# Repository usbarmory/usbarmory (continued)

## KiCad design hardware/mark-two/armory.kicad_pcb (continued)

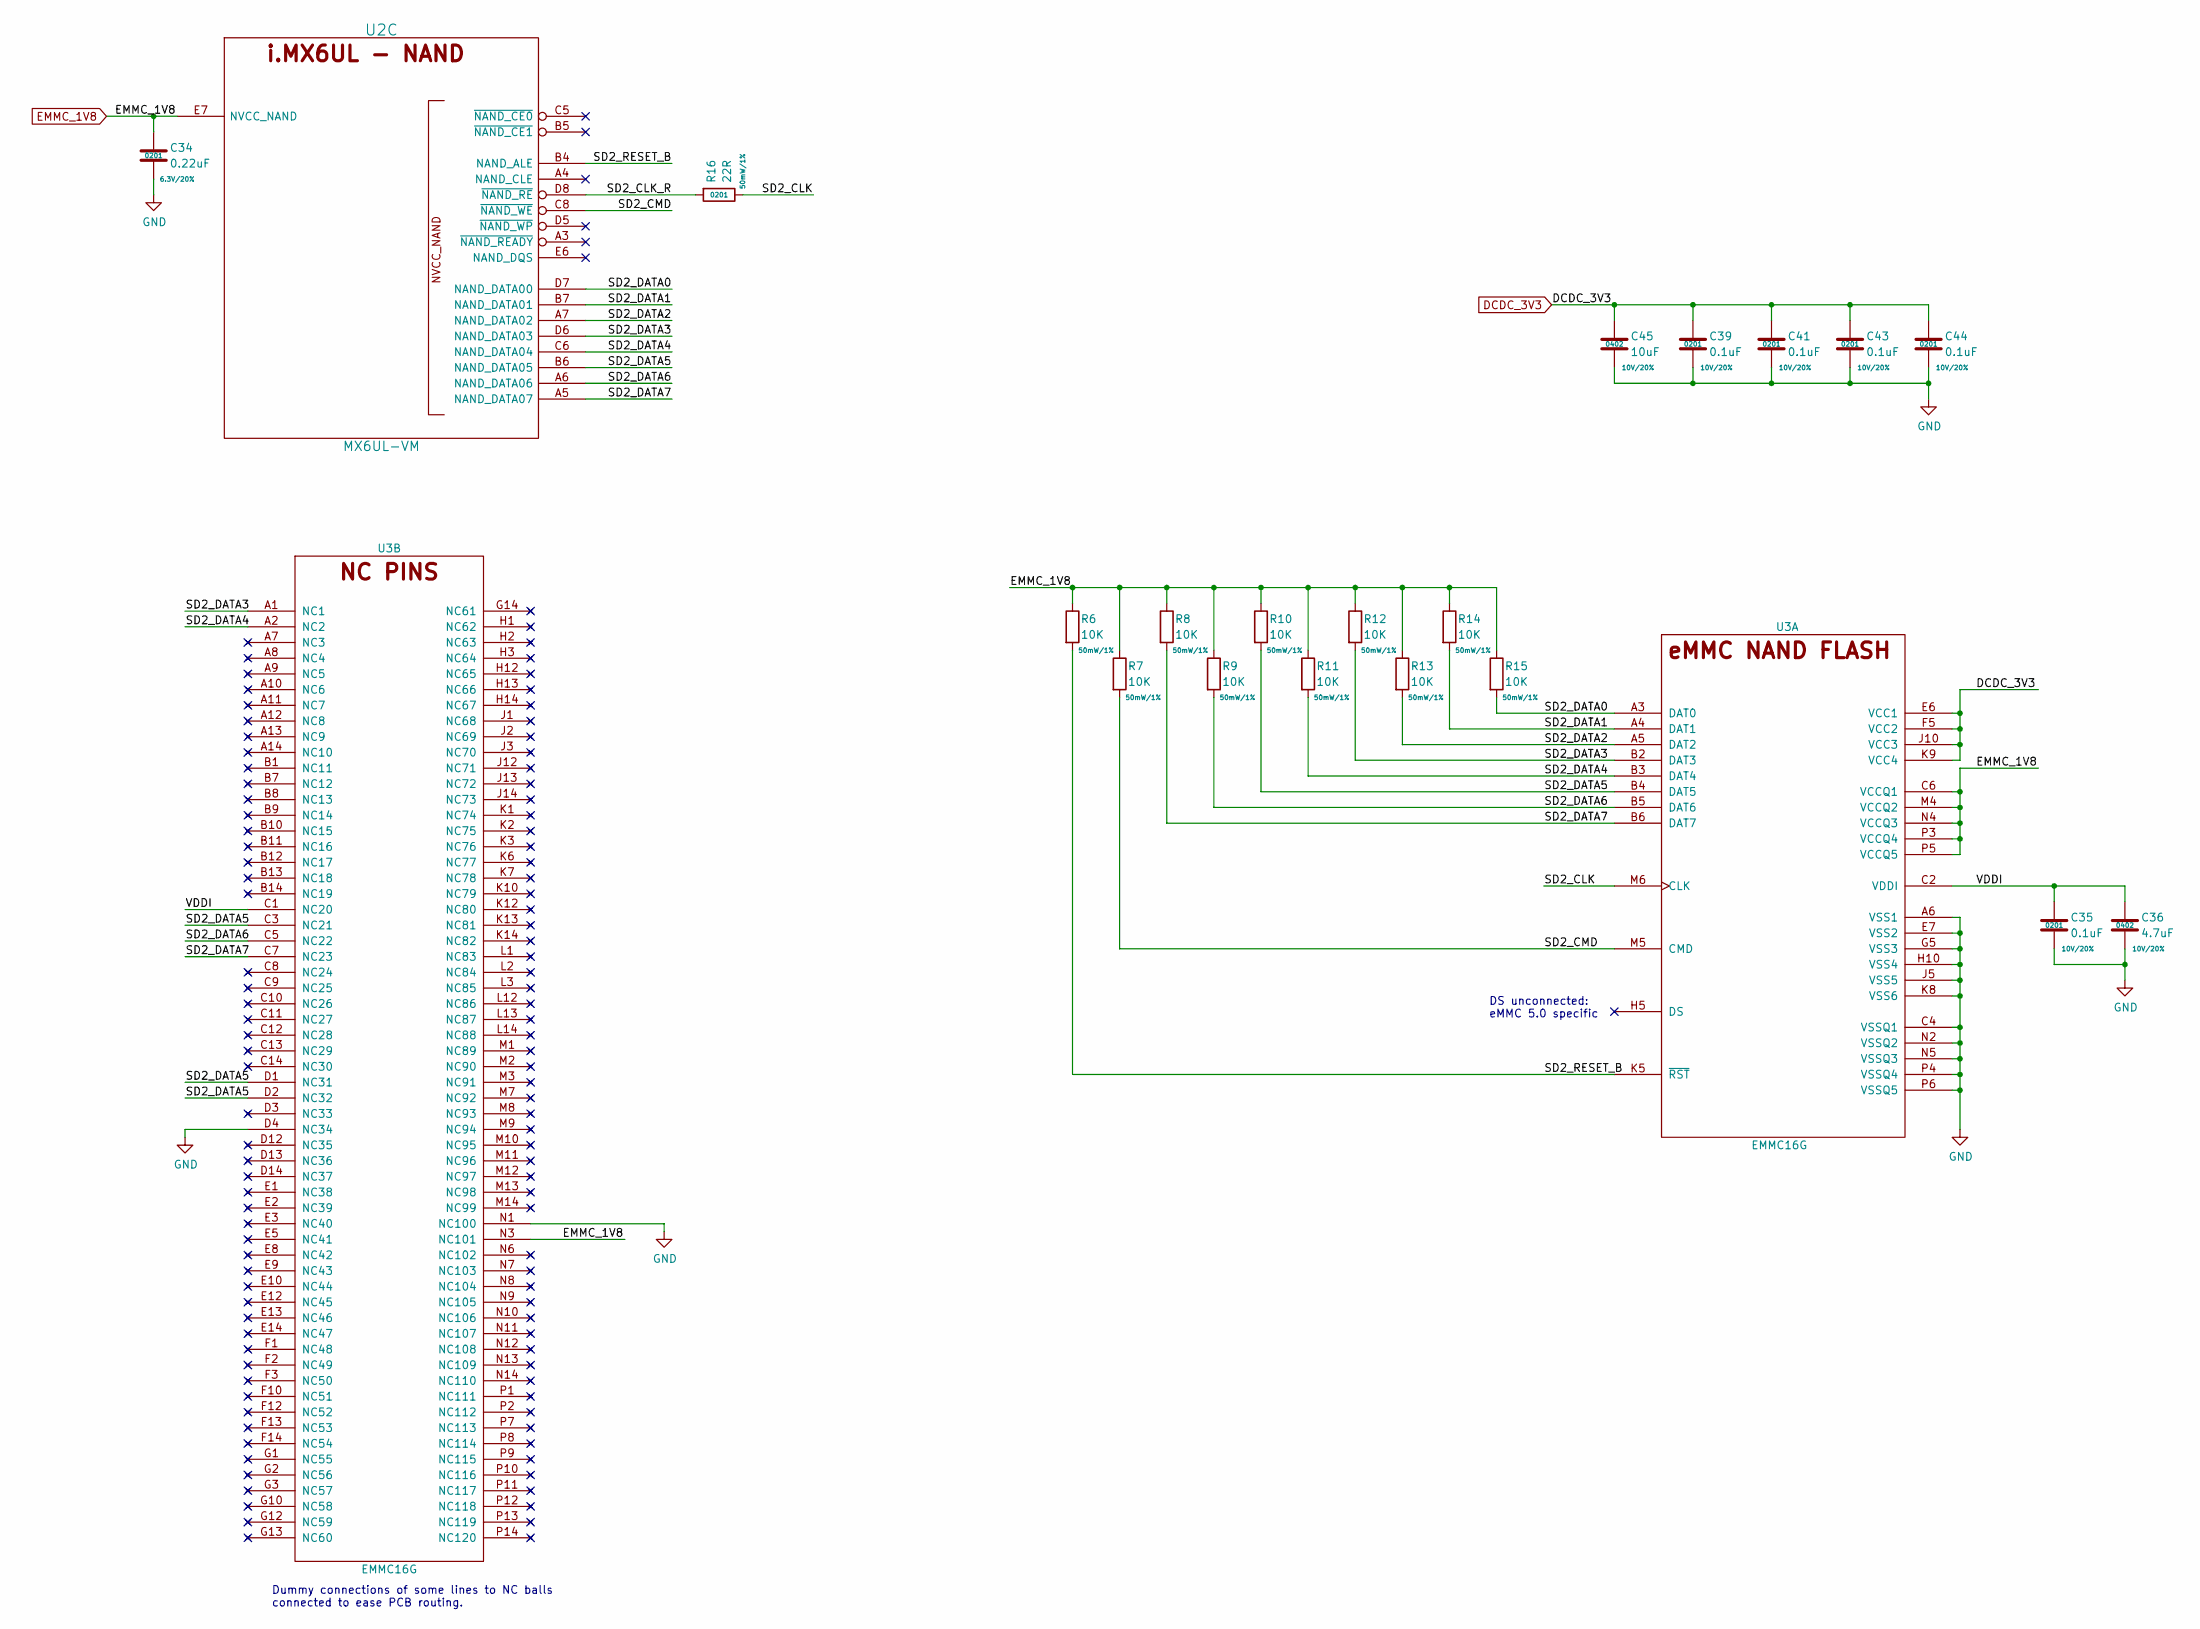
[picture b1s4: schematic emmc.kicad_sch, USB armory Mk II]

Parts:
C34: 0.22uF; SM0201; Rating 6.3V/20%; Mfg PN GRM033R60J224ME15D
C35, C39, C41, C43, C44: 0.1uF; SM0201; Rating 10V/20%; Mfg PN GRM033R61A104ME15D
C36: 4.7uF; SM0402; Rating 10V/20%; Mfg PN ZRB15XR61A475ME01D
C45: 10uF; SM0402; Rating 10V/20%; Mfg PN CL05A106MP8NUB8
R6, R7, R8, R9, R10, R11, R12, R13, R14, R15: 10K; SM0201; Rating 50mW/1%; Mfg PN CRCW020110K0JNED
R16: 22R; SM0201; Rating 50mW/1%; Mfg PN CRCW020122R0JNED
U2: MX6UL-VM; SOT1534-2; Mfg PN MCIMX6Z0DVM09AB
U3: EMMC16G; FBGA-153; Mfg PN EMMC16G-TB29-PZ90

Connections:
/eMMC/SD2_CLK: R16.1, U3.M6 (CLK)
/eMMC/SD2_CLK_R: R16.2, U2.D8 (~NAND_RE)
/eMMC/SD2_CMD: R7.2, U2.C8 (~NAND_WE), U3.M5 (CMD)
/eMMC/SD2_DATA0: R15.2, U2.D7 (NAND_DATA00), U3.A3 (DAT0)
/eMMC/SD2_DATA1: R14.2, U2.B7 (NAND_DATA01), U3.A4 (DAT1)
/eMMC/SD2_DATA2: R13.2, U2.A7 (NAND_DATA02), U3.A5 (DAT2)
/eMMC/SD2_DATA3: R12.2, U2.D6 (NAND_DATA03), U3.A1 (NC1), U3.B2 (DAT3)
/eMMC/SD2_DATA4: R11.2, U2.C6 (NAND_DATA04), U3.A2 (NC2), U3.B3 (DAT4)
/eMMC/SD2_DATA5: R10.2, U2.B6 (NAND_DATA05), U3.B4 (DAT5), U3.C3 (NC21), U3.D1 (NC31), U3.D2 (NC32)
/eMMC/SD2_DATA6: R9.2, U2.A6 (NAND_DATA06), U3.B5 (DAT6), U3.C5 (NC22)
/eMMC/SD2_DATA7: R8.2, U2.A5 (NAND_DATA07), U3.B6 (DAT7), U3.C7 (NC23)
/eMMC/SD2_RESET_B: R6.2, U2.B4 (NAND_ALE), U3.K5 (~RST)
/eMMC/VDDI: C35.1, C36.1, U3.C1 (NC20), U3.C2 (VDDI)
DCDC_3V3: C39.1, C41.1, C43.1, C44.1, C45.1, U3.E6 (VCC1), U3.F5 (VCC2), U3.J10 (VCC3), U3.K9 (VCC4); also elsewhere on the board
EMMC_1V8: C34.1, R6.1, R7.1, R8.1, R9.1, R10.1, R11.1, R12.1, R13.1, R14.1, R15.1, U2.E7 (NVCC_NAND), U3.C6 (VCCQ1), U3.M4 (VCCQ2), U3.N3 (NC101), U3.N4 (VCCQ3), U3.P3 (VCCQ4), U3.P5 (VCCQ5); also elsewhere on the board
GND: C34.2, C35.2, C36.2, C39.2, C41.2, C43.2, C44.2, C45.2, U3.A6 (VSS1), U3.C4 (VSSQ1), U3.D4 (NC34), U3.E7 (VSS2), U3.G5 (VSS3), U3.H10 (VSS4), U3.J5 (VSS5), U3.K8 (VSS6), U3.N1 (NC100), U3.N2 (VSSQ2), U3.N5 (VSSQ3), U3.P4 (VSSQ4), U3.P6 (VSSQ5); also elsewhere on the board

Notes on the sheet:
Dummy connections of some lines to NC balls connected to ease PCB routing.
DS unconnected: eMMC 5.0 specific

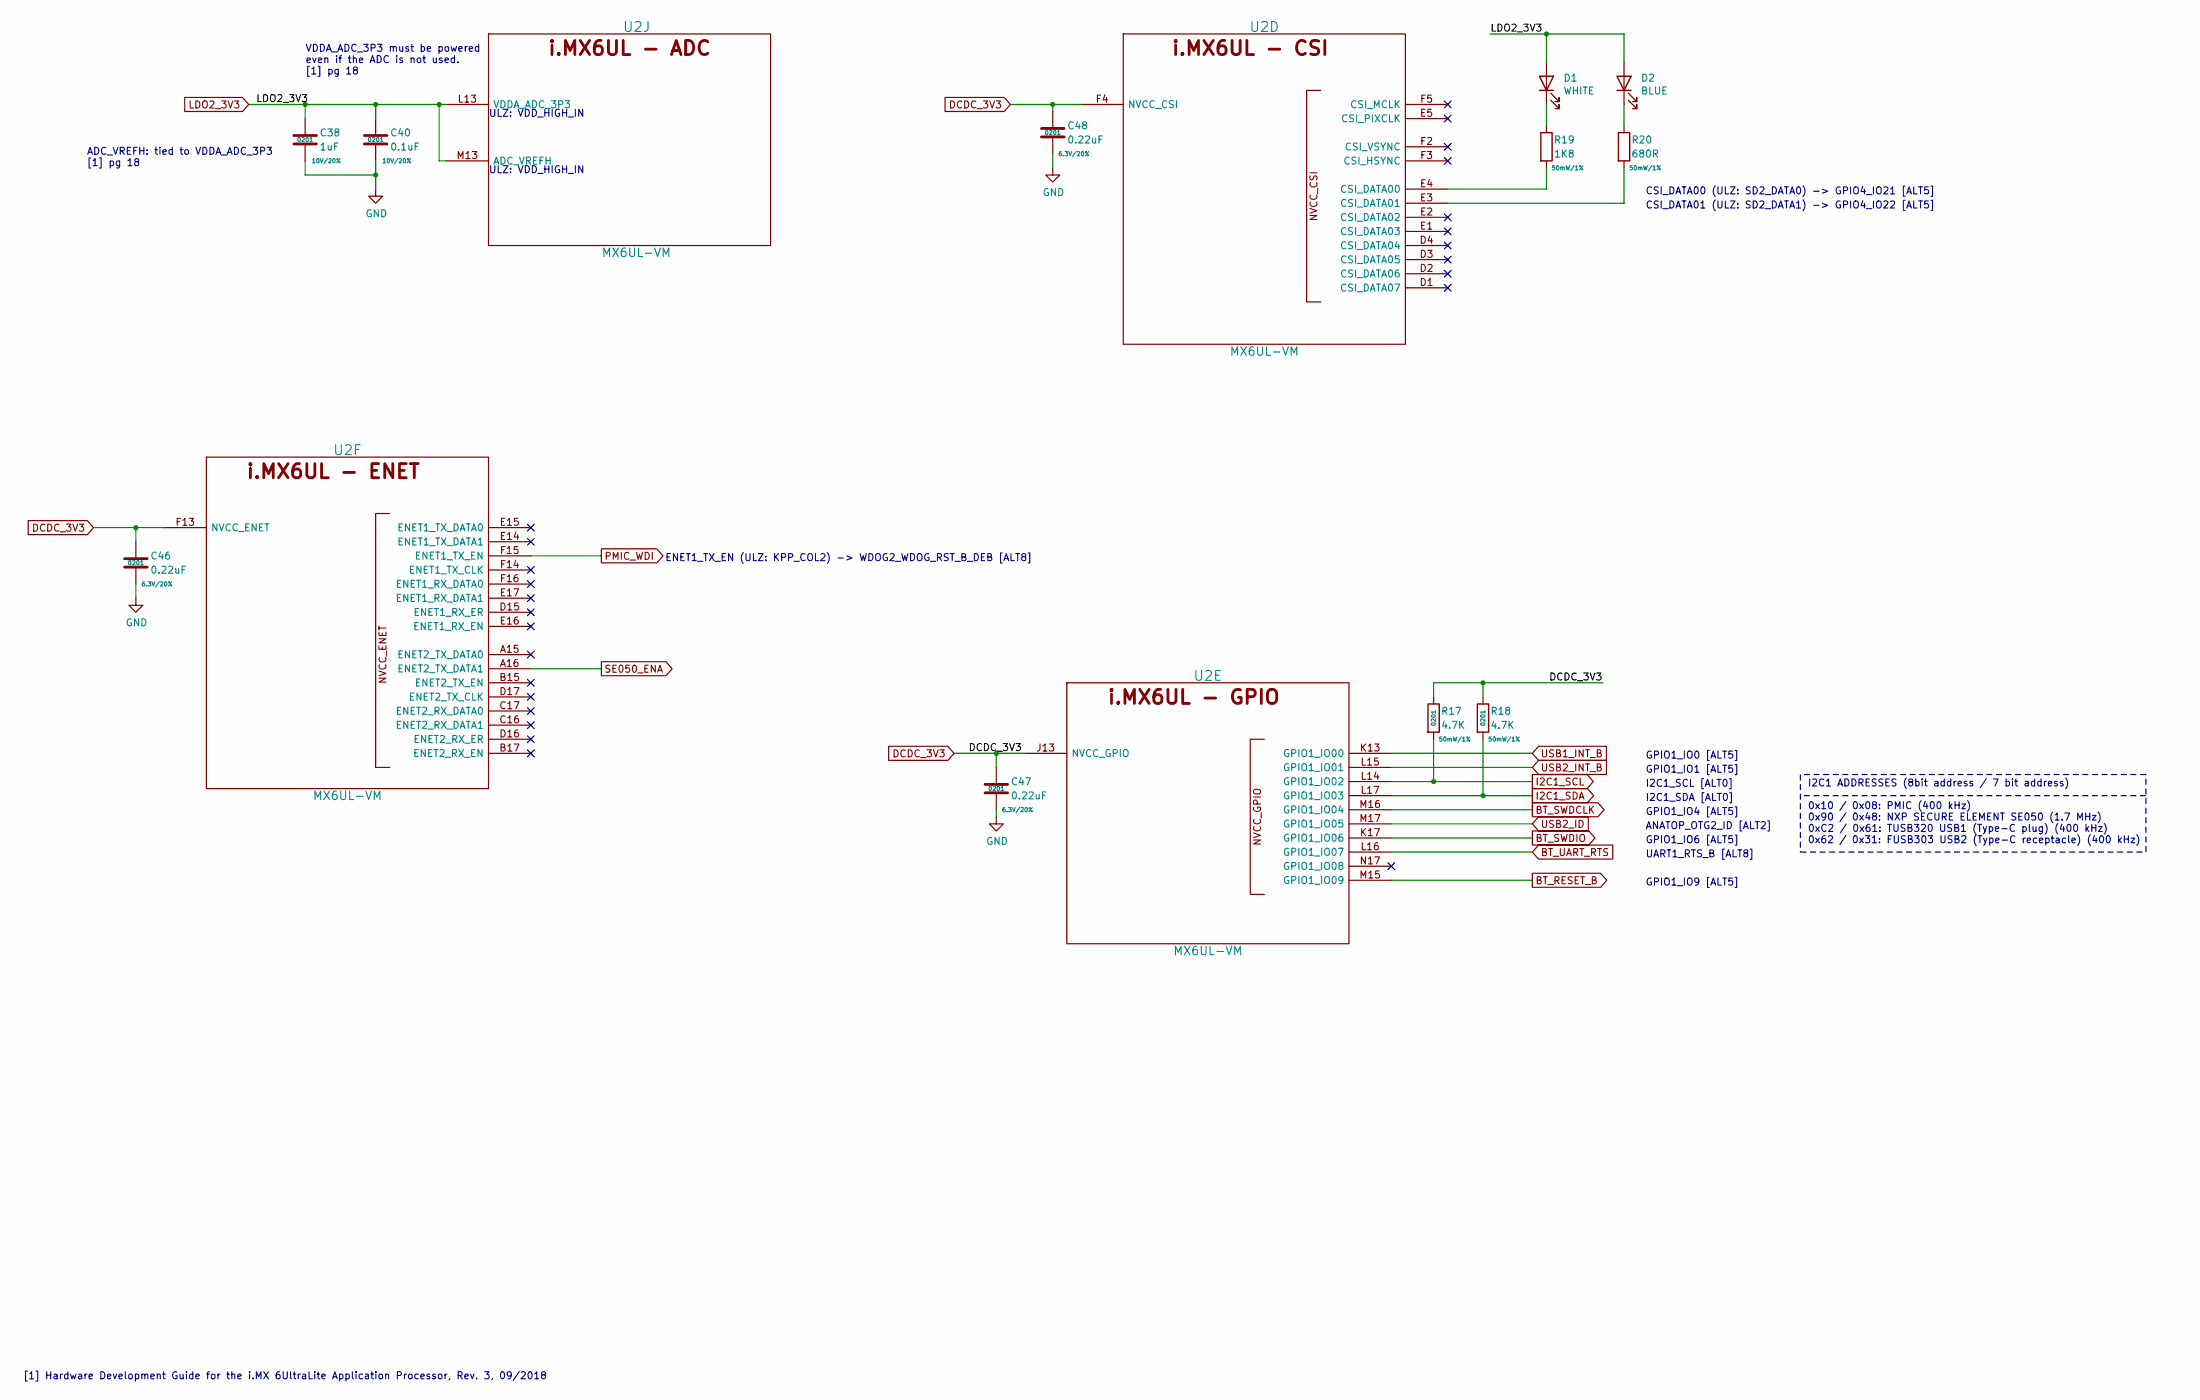
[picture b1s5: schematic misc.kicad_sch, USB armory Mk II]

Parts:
C38: 1uF; SM0201; Rating 10V/20%; Mfg PN GRM033R61A105ME15D
C40: 0.1uF; SM0201; Rating 10V/20%; Mfg PN GRM033R61A104ME15D
C46, C47, C48: 0.22uF; SM0201; Rating 6.3V/20%; Mfg PN GRM033R60J224ME15D
D1: WHITE; SM0603_LED; Rating 5mA/2.85V; Mfg PN LW Q38E-Q1OO-3K6L-1
D2: BLUE; SM0603_LED; Rating 5mA/2.85V; Mfg PN LB Q39G-L2OO-35-1
R17, R18: 4.7K; SM0201; Rating 50mW/1%; Mfg PN CRCW02014K70JNED
R19: 1K8; SM0201; Rating 50mW/1%; Mfg PN ERJ-1GNF1801C
R20: 680R; SM0201; Rating 50mW/1%; Mfg PN ERJ-1GNF6800C
U2: MX6UL-VM; SOT1534-2; Mfg PN MCIMX6Z0DVM09AB

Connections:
BT_RESET_B: U2.M15 (GPIO1_IO09); also elsewhere on the board
BT_SWDCLK: U2.M16 (GPIO1_IO04); also elsewhere on the board
BT_SWDIO: U2.K17 (GPIO1_IO06); also elsewhere on the board
BT_UART_RTS: U2.L16 (GPIO1_IO07); also elsewhere on the board
DCDC_3V3: C46.1, C47.1, C48.1, R17.1, R18.1, U2.F4 (NVCC_CSI), U2.F13 (NVCC_ENET), U2.J13 (NVCC_GPIO); also elsewhere on the board
GND: C38.2, C40.2, C46.2, C47.2, C48.2; also elsewhere on the board
I2C1_SCL: R17.2, U2.L14 (GPIO1_IO02); also elsewhere on the board
I2C1_SDA: R18.2, U2.L17 (GPIO1_IO03); also elsewhere on the board
LDO2_3V3: C38.1, C40.1, D1.2 (A), D2.2 (A), U2.L13 (VDDA_ADC_3P3), U2.M13 (ADC_VREFH); also elsewhere on the board
unnamed: D1.1 (K), R19.1
unnamed: D2.1 (K), R20.1
unnamed: R19.2, U2.E4 (CSI_DATA00)
unnamed: R20.2, U2.E3 (CSI_DATA01)
PMIC_WDI: U2.F15 (ENET1_TX_EN); also elsewhere on the board
SE050_ENA: U2.A16 (ENET2_TX_DATA1); also elsewhere on the board
USB1_INT_B: U2.K13 (GPIO1_IO00); also elsewhere on the board
USB2_ID: U2.M17 (GPIO1_IO05); also elsewhere on the board
USB2_INT_B: U2.L15 (GPIO1_IO01); also elsewhere on the board

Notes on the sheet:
CSI_DATA01 (ULZ: SD2_DATA1) -> GPIO4_IO22 [ALT5]
VDDA_ADC_3P3 must be powered even if the ADC is not used. [1] pg 18
ULZ: VDD_HIGH_IN
I2C1_SDA [ALT0]
GPIO1_IO4 [ALT5]
GPIO1_IO1 [ALT5]
GPIO1_IO6 [ALT5]
GPIO1_IO0 [ALT5]
GPIO1_IO9 [ALT5]
[1] Hardware Development Guide for the i.MX 6UltraLite Application Processor, Rev. 3, 09/2018
CSI_DATA00 (ULZ: SD2_DATA0) -> GPIO4_IO21 [ALT5]
ANATOP_OTG2_ID [ALT2]
ADC_VREFH: tied to VDDA_ADC_3P3 [1] pg 18
UART1_RTS_B [ALT8]
ENET1_TX_EN (ULZ: KPP_COL2) -> WDOG2_WDOG_RST_B_DEB [ALT8]
I2C1 ADDRESSES (8bit address / 7 bit address) 0x10 / 0x08: PMIC (400 kHz) 0x90 / 0x48: NXP SECURE ELEMENT SE050 (1.7 MHz) 0xC2 / 0x61: TUSB320 USB1 (Type-C plug) (400 kHz) 0x62 / 0x31: FUSB303 USB2 (Type-C receptacle) (400 kHz)
I2C1_SCL [ALT0]

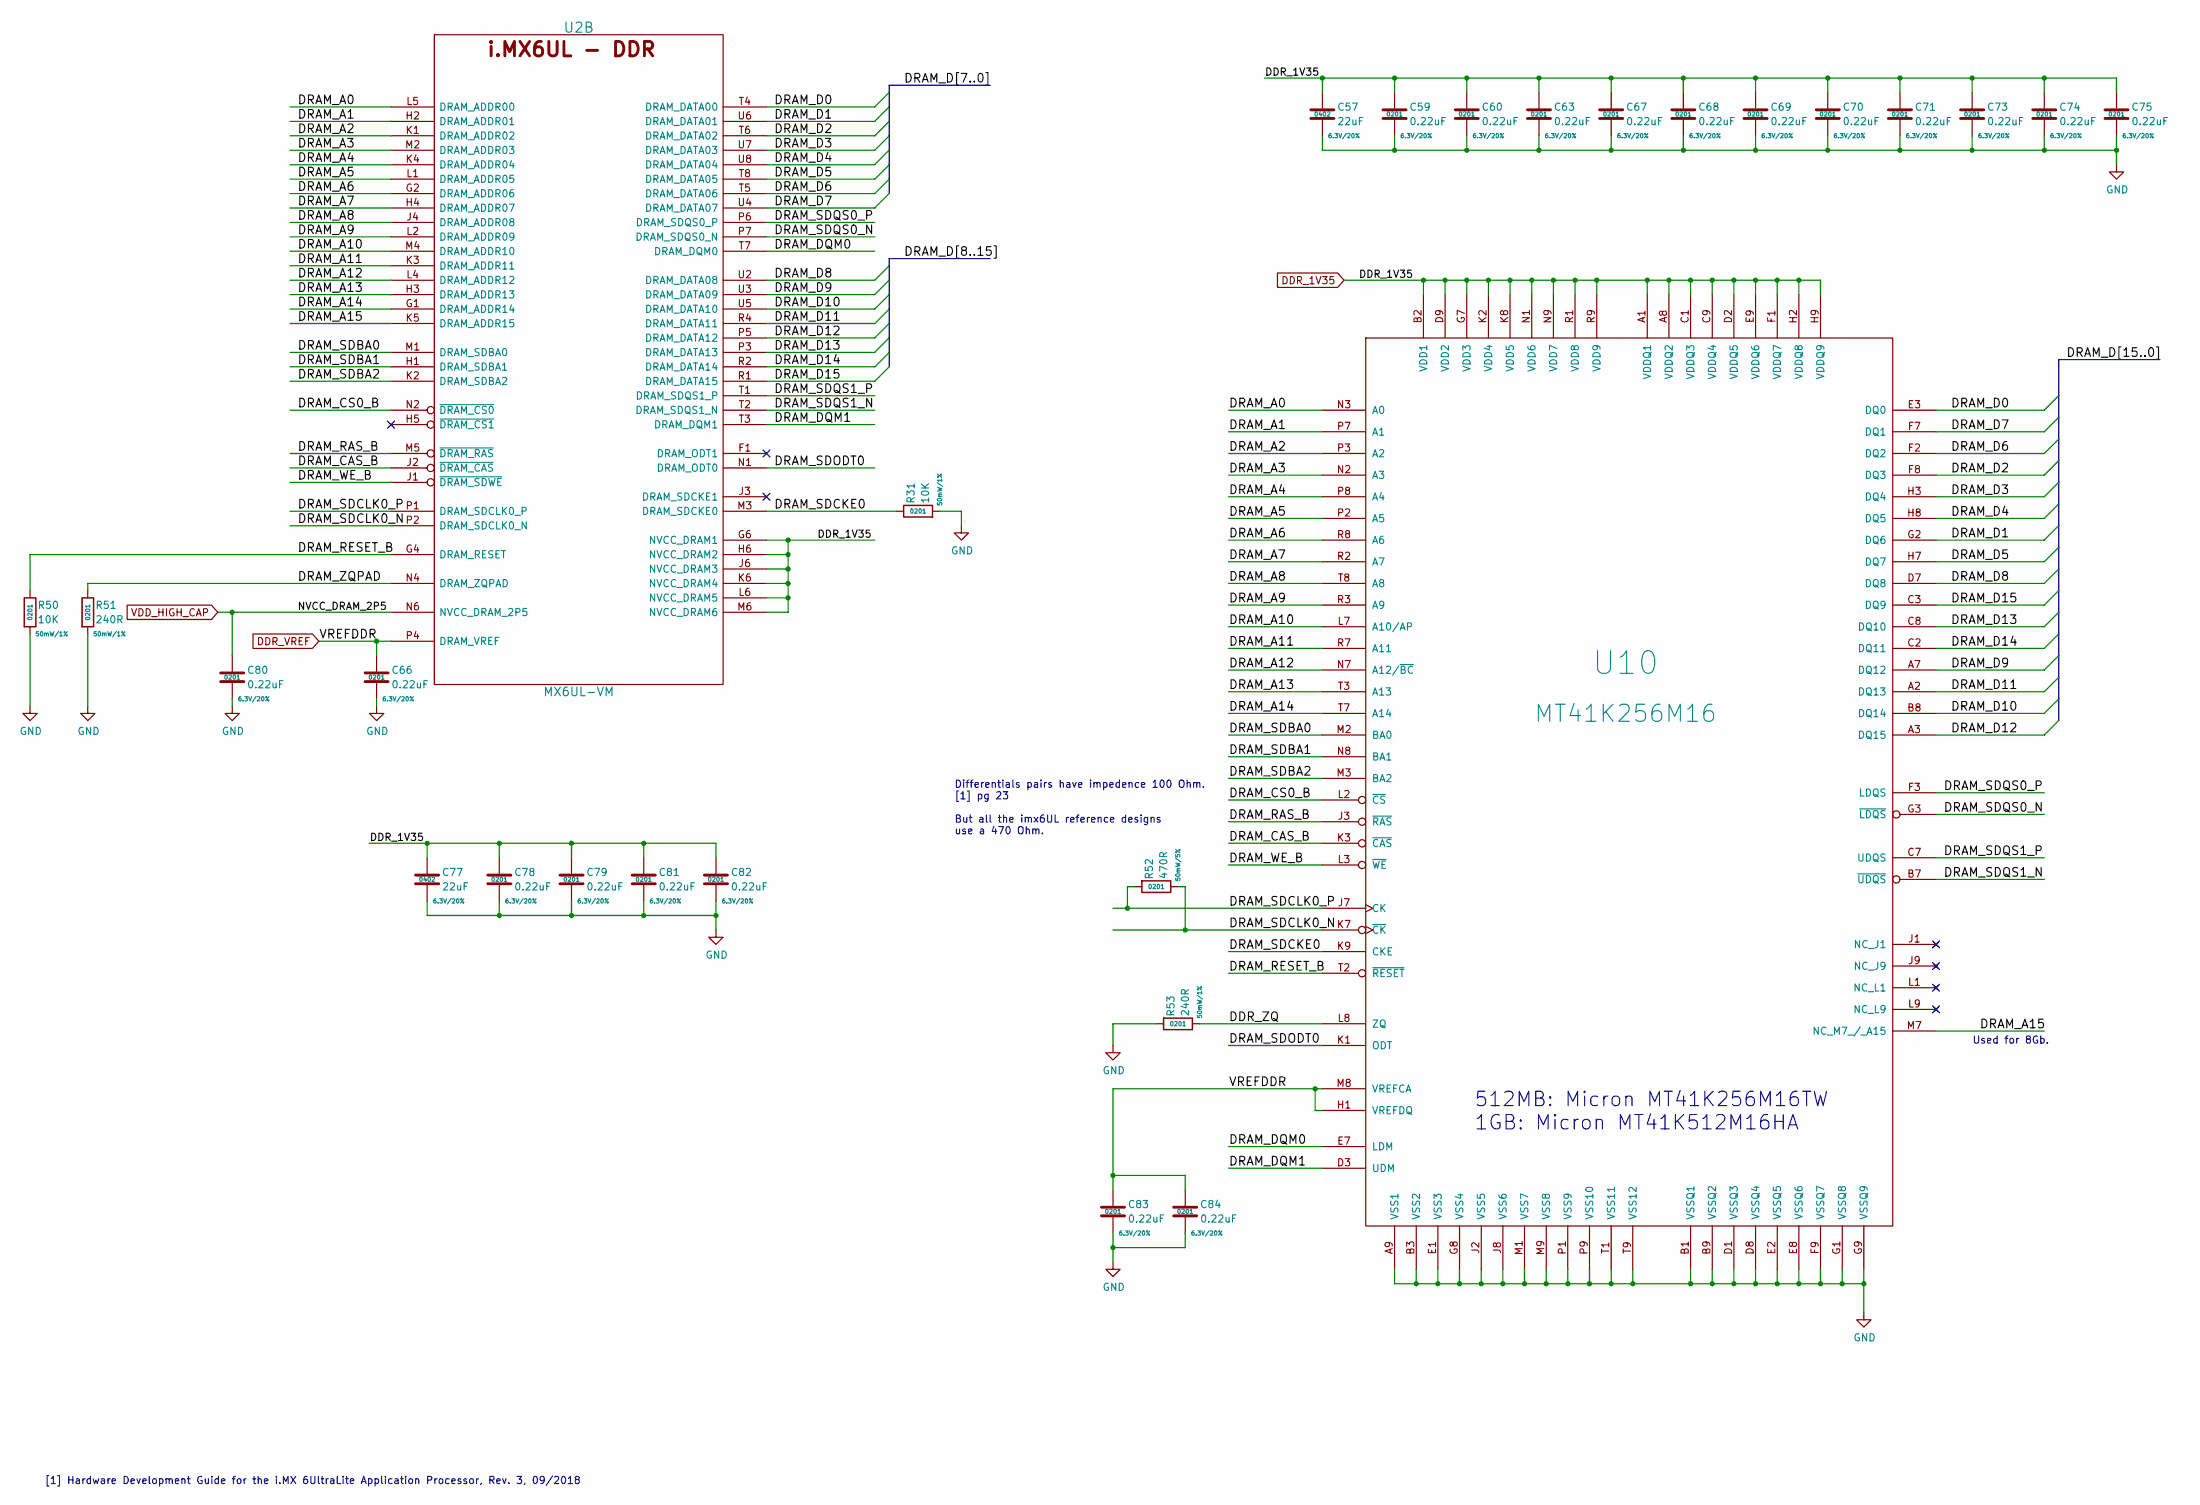
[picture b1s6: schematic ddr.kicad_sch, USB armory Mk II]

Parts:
C57, C77: 22uF; SM0402; Rating 6.3V/20%; Mfg PN CL05A226MQ5N6J8
C59, C60, C63, C66, C67, C68, C69, C70, C71, C73, C74, C75, C78, C79, C80, C81, C82, C83, C84: 0.22uF; SM0201; Rating 6.3V/20%; Mfg PN GRM033R60J224ME15D
R31, R50: 10K; SM0201; Rating 50mW/1%; Mfg PN CRCW020110K0JNED
R51, R53: 240R; SM0201; Rating 50mW/1%; Mfg PN CRCW0201240RFNED
R52: 470R; SM0201; Rating 50mW/5%; Mfg PN CRCW0201470RJNED
U2: MX6UL-VM; SOT1534-2; Mfg PN MCIMX6Z0DVM09AB
U10: MT41K256M16; MICRON-FBGA-96; Mfg PN MT41K256M16TW-107:P

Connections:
/DDR/DDR_ZQ: R53.1, U10.L8 (ZQ)
/DDR/DRAM_A0: U2.L5 (DRAM_ADDR00), U10.N3 (A0)
/DDR/DRAM_A1: U2.H2 (DRAM_ADDR01), U10.P7 (A1)
/DDR/DRAM_A2: U2.K1 (DRAM_ADDR02), U10.P3 (A2)
/DDR/DRAM_A3: U2.M2 (DRAM_ADDR03), U10.N2 (A3)
/DDR/DRAM_A4: U2.K4 (DRAM_ADDR04), U10.P8 (A4)
/DDR/DRAM_A5: U2.L1 (DRAM_ADDR05), U10.P2 (A5)
/DDR/DRAM_A6: U2.G2 (DRAM_ADDR06), U10.R8 (A6)
/DDR/DRAM_A7: U2.H4 (DRAM_ADDR07), U10.R2 (A7)
/DDR/DRAM_A8: U2.J4 (DRAM_ADDR08), U10.T8 (A8)
/DDR/DRAM_A9: U2.L2 (DRAM_ADDR09), U10.R3 (A9)
/DDR/DRAM_A10: U2.M4 (DRAM_ADDR10), U10.L7 (A10/AP)
/DDR/DRAM_A11: U2.K3 (DRAM_ADDR11), U10.R7 (A11)
/DDR/DRAM_A12: U2.L4 (DRAM_ADDR12), U10.N7 (A12/~BC)
/DDR/DRAM_A13: U2.H3 (DRAM_ADDR13), U10.T3 (A13)
/DDR/DRAM_A14: U2.G1 (DRAM_ADDR14), U10.T7 (A14)
/DDR/DRAM_A15: U2.K5 (DRAM_ADDR15), U10.M7 (NC_M7_/_A15)
/DDR/DRAM_CAS_B: U2.J2 (~DRAM_CAS), U10.K3 (~CAS)
/DDR/DRAM_CS0_B: U2.N2 (~DRAM_CS0), U10.L2 (~CS)
/DDR/DRAM_D0: U2.T4 (DRAM_DATA00), U10.E3 (DQ0)
/DDR/DRAM_D1: U2.U6 (DRAM_DATA01), U10.G2 (DQ6)
/DDR/DRAM_D2: U2.T6 (DRAM_DATA02), U10.F8 (DQ3)
/DDR/DRAM_D3: U2.U7 (DRAM_DATA03), U10.H3 (DQ4)
/DDR/DRAM_D4: U2.U8 (DRAM_DATA04), U10.H8 (DQ5)
/DDR/DRAM_D5: U2.T8 (DRAM_DATA05), U10.H7 (DQ7)
/DDR/DRAM_D6: U2.T5 (DRAM_DATA06), U10.F2 (DQ2)
/DDR/DRAM_D7: U2.U4 (DRAM_DATA07), U10.F7 (DQ1)
/DDR/DRAM_D8: U2.U2 (DRAM_DATA08), U10.D7 (DQ8)
/DDR/DRAM_D9: U2.U3 (DRAM_DATA09), U10.A7 (DQ12)
/DDR/DRAM_D10: U2.U5 (DRAM_DATA10), U10.B8 (DQ14)
/DDR/DRAM_D11: U2.R4 (DRAM_DATA11), U10.A2 (DQ13)
/DDR/DRAM_D12: U2.P5 (DRAM_DATA12), U10.A3 (DQ15)
/DDR/DRAM_D13: U2.P3 (DRAM_DATA13), U10.C8 (DQ10)
/DDR/DRAM_D14: U2.R2 (DRAM_DATA14), U10.C2 (DQ11)
/DDR/DRAM_D15: U2.R1 (DRAM_DATA15), U10.C3 (DQ9)
/DDR/DRAM_DQM0: U2.T7 (DRAM_DQM0), U10.E7 (LDM)
/DDR/DRAM_DQM1: U2.T3 (DRAM_DQM1), U10.D3 (UDM)
/DDR/DRAM_RAS_B: U2.M5 (~DRAM_RAS), U10.J3 (~RAS)
/DDR/DRAM_RESET_B: R50.1, U2.G4 (DRAM_RESET), U10.T2 (~RESET)
/DDR/DRAM_SDBA0: U2.M1 (DRAM_SDBA0), U10.M2 (BA0)
/DDR/DRAM_SDBA1: U2.H1 (DRAM_SDBA1), U10.N8 (BA1)
/DDR/DRAM_SDBA2: U2.K2 (DRAM_SDBA2), U10.M3 (BA2)
/DDR/DRAM_SDCKE0: R31.1, U2.M3 (DRAM_SDCKE0), U10.K9 (CKE)
/DDR/DRAM_SDCLK0_N: R52.1, U2.P2 (DRAM_SDCLK0_N), U10.K7 (~CK)
/DDR/DRAM_SDCLK0_P: R52.2, U2.P1 (DRAM_SDCLK0_P), U10.J7 (CK)
/DDR/DRAM_SDODT0: U2.N1 (DRAM_ODT0), U10.K1 (ODT)
/DDR/DRAM_SDQS0_N: U2.P7 (DRAM_SDQS0_N), U10.G3 (~LDQS)
/DDR/DRAM_SDQS0_P: U2.P6 (DRAM_SDQS0_P), U10.F3 (LDQS)
/DDR/DRAM_SDQS1_N: U2.T2 (DRAM_SDQS1_N), U10.B7 (~UDQS)
/DDR/DRAM_SDQS1_P: U2.T1 (DRAM_SDQS1_P), U10.C7 (UDQS)
/DDR/DRAM_WE_B: U2.J1 (~DRAM_SDWE), U10.L3 (~WE)
/DDR/DRAM_ZQPAD: R51.1, U2.N4 (DRAM_ZQPAD)
DDR_1V35: C57.1, C59.1, C60.1, C63.1, C67.1, C68.1, C69.1, C70.1, C71.1, C73.1, C74.1, C75.1, C77.1, C78.1, C79.1, C81.1, C82.1, U2.G6 (NVCC_DRAM1), U2.H6 (NVCC_DRAM2), U2.J6 (NVCC_DRAM3), U2.K6 (NVCC_DRAM4), U2.L6 (NVCC_DRAM5), U2.M6 (NVCC_DRAM6), U10.A1 (VDDQ1), U10.A8 (VDDQ2), U10.B2 (VDD1), U10.C1 (VDDQ3), U10.C9 (VDDQ4), U10.D2 (VDDQ5), U10.D9 (VDD2), U10.E9 (VDDQ6), U10.F1 (VDDQ7), U10.G7 (VDD3), U10.H2 (VDDQ8), U10.H9 (VDDQ9), U10.K2 (VDD4), U10.K8 (VDD5), U10.N1 (VDD6), U10.N9 (VDD7), U10.R1 (VDD8), U10.R9 (VDD9); also elsewhere on the board
DDR_VREF: C66.1, C83.1, C84.1, U2.P4 (DRAM_VREF), U10.H1 (VREFDQ), U10.M8 (VREFCA); also elsewhere on the board
GND: C57.2, C59.2, C60.2, C63.2, C66.2, C67.2, C68.2, C69.2, C70.2, C71.2, C73.2, C74.2, C75.2, C77.2, C78.2, C79.2, C80.2, C81.2, C82.2, C83.2, C84.2, R31.2, R50.2, R51.2, R53.2, U10.A9 (VSS1), U10.B1 (VSSQ1), U10.B3 (VSS2), U10.B9 (VSSQ2), U10.D1 (VSSQ3), U10.D8 (VSSQ4), U10.E1 (VSS3), U10.E2 (VSSQ5), U10.E8 (VSSQ6), U10.F9 (VSSQ7), U10.G1 (VSSQ8), U10.G8 (VSS4), U10.G9 (VSSQ9), U10.J2 (VSS5), U10.J8 (VSS6), U10.M1 (VSS7), U10.M9 (VSS8), U10.P1 (VSS9), U10.P9 (VSS10), U10.T1 (VSS11), U10.T9 (VSS12); also elsewhere on the board
VDD_HIGH_CAP: C80.1, U2.N6 (NVCC_DRAM_2P5); also elsewhere on the board

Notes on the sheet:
Used for 8Gb.
Differentials pairs have impedence 100 Ohm. [1] pg 23 But all the imx6UL reference designs use a 470 Ohm.
[1] Hardware Development Guide for the i.MX 6UltraLite Application Processor, Rev. 3, 09/2018
512MB: Micron MT41K256M16TW 1GB: Micron MT41K512M16HA

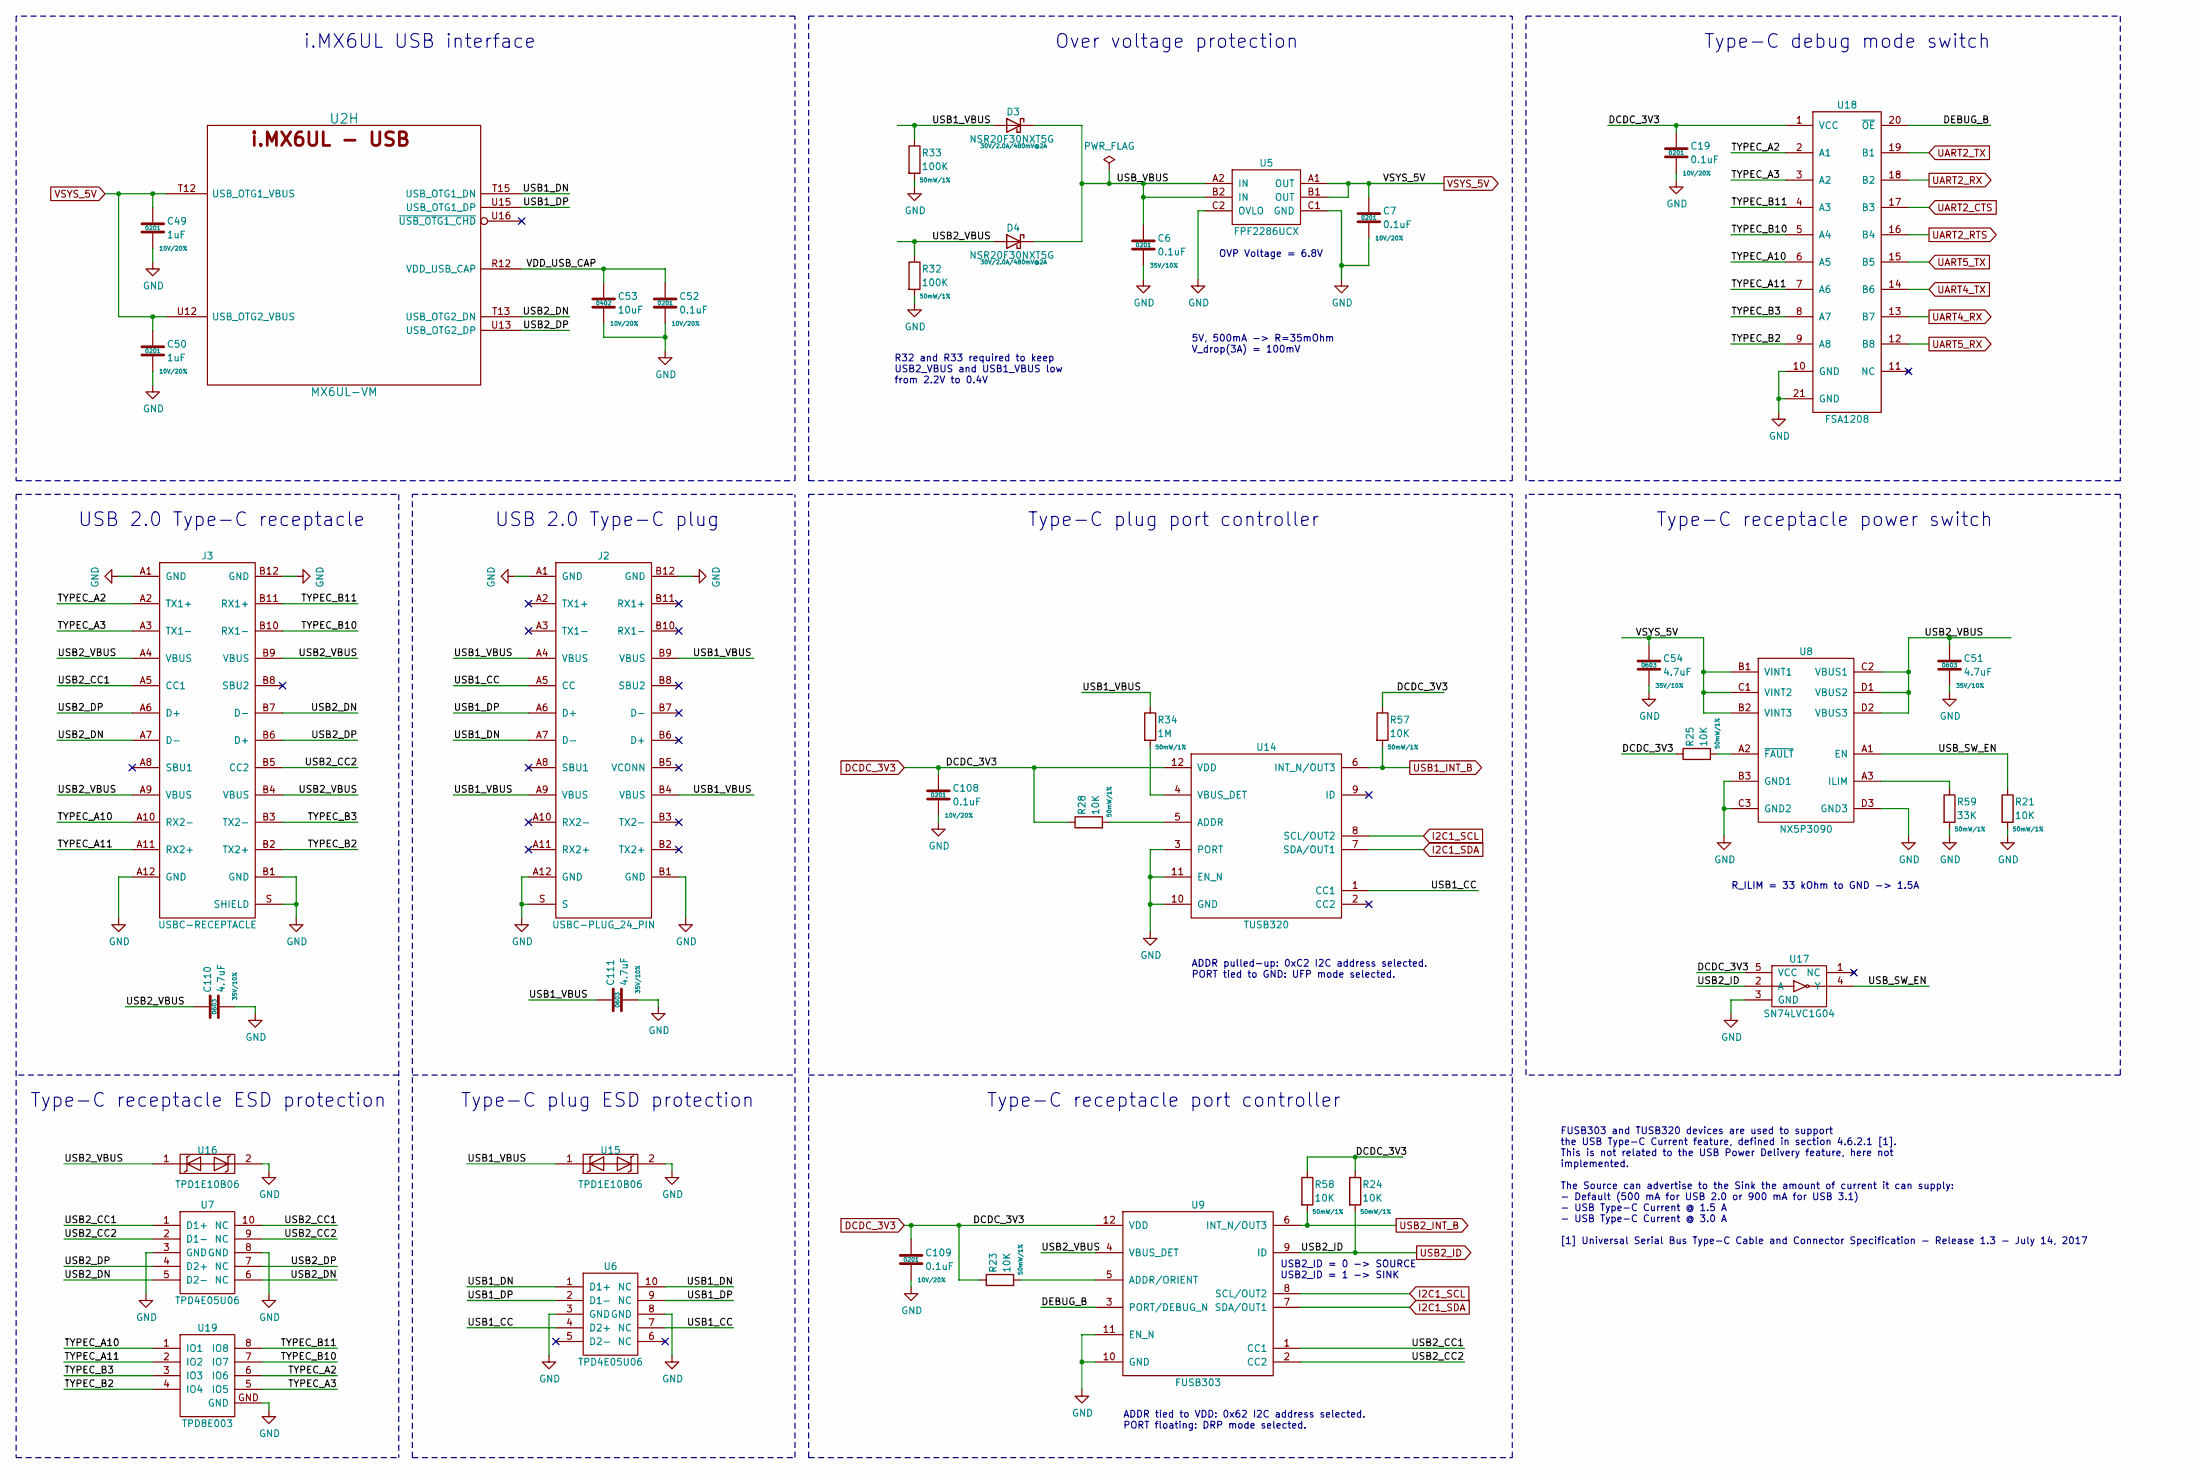
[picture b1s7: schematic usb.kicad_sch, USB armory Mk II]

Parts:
C6: 0.1uF; SM0201; Rating 35V/10%; Mfg PN GRM033R61A104ME15D
C7, C19, C52, C108, C109: 0.1uF; SM0201; Rating 10V/20%; Mfg PN GRM033R61A104ME15D
C49, C50: 1uF; SM0201; Rating 10V/20%; Mfg PN GRM033R61A105ME15D
C51, C54, C110, C111: 4.7uF; SM0603; Rating 35V/10%; Mfg PN GRM188R6YA475KE15D
C53: 10uF; SM0402; Rating 10V/20%; Mfg PN CL05A106MP8NUB8
D3, D4: NSR20F30NXT5G; DSN2; Rating 30V/2.0A/480mV@2A; Mfg PN NSR20F30NXT5G
J2: USBC-PLUG_24_PIN; WURTH_632712000112; Mfg PN 632712000112
J3: USBC-RECEPTACLE; MOLEX_105450-0101; Mfg PN 105450-0101
R21, R23, R24, R25, R28, R57, R58: 10K; SM0201; Rating 50mW/1%; Mfg PN CRCW020110K0JNED
R32, R33: 100K; SM0201; Rating 50mW/1%; Mfg PN CRCW0201100KJNED
R34: 1M; SM0201; Rating 50mW/1%; Mfg PN CRCW02011M00FKED
R59: 33K; SM0201; Rating 50mW/1%; Mfg PN CRCW020133K0FKED
U2: MX6UL-VM; SOT1534-2; Mfg PN MCIMX6Z0DVM09AB
U5: FPF2286UCX; WLCSP-6; Mfg PN FPF2286UCX
U6, U7: TPD4E05U06; DQA-USON-10; Mfg PN TPD4E05U06DQAR
U8: NX5P3090; SOT1390-5; Mfg PN NX5P3090UKZ
U9: FUSB303; RWB-QFN-12; Mfg PN FUSB303TMX
U14: TUSB320; RWB-QFN-12; Mfg PN TUSB320IRWBR
U15, U16: TPD1E10B06; X1SON-2; Mfg PN TPD1E10B06DPYR
U17: SN74LVC1G04; X2SON-4; Mfg PN SN74LVC1G04DPWR
U18: FSA1208; MLP-20; Mfg PN FSA1208BQX
U19: TPD8E003; WSON-8; Mfg PN TPD8E003DQDR

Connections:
/USB/DEBUG_B: U9.3 (PORT/DEBUG_N), U18.20 (~OE)
/USB/TYPEC_A2: J3.A2 (TX1+), U18.2 (A1), U19.6 (IO6)
/USB/TYPEC_A3: J3.A3 (TX1-), U18.3 (A2), U19.5 (IO5)
/USB/TYPEC_A10: J3.A10 (RX2-), U18.6 (A5), U19.1 (IO1)
/USB/TYPEC_A11: J3.A11 (RX2+), U18.7 (A6), U19.2 (IO2)
/USB/TYPEC_B2: J3.B2 (TX2+), U18.9 (A8), U19.4 (IO4)
/USB/TYPEC_B3: J3.B3 (TX2-), U18.8 (A7), U19.3 (IO3)
/USB/TYPEC_B10: J3.B10 (RX1-), U18.5 (A4), U19.7 (IO7)
/USB/TYPEC_B11: J3.B11 (RX1+), U18.4 (A3), U19.8 (IO8)
/USB/USB1_CC: J2.A5 (CC), U6.4 (D2+), U6.7 (NC), U14.1 (CC1)
/USB/USB1_DN: J2.A7 (D-), U2.T15 (USB_OTG1_DN), U6.1 (D1+), U6.10 (NC)
/USB/USB1_DP: J2.A6 (D+), U2.U15 (USB_OTG1_DP), U6.2 (D1-), U6.9 (NC)
/USB/USB1_VBUS: C111.1, D3.2 (A), J2.A4 (VBUS), J2.A9 (VBUS), J2.B4 (VBUS), J2.B9 (VBUS), R33.1, R34.1, U15.1
/USB/USB2_CC1: J3.A5 (CC1), U7.1 (D1+), U7.10 (NC), U9.1 (CC1)
/USB/USB2_CC2: J3.B5 (CC2), U7.2 (D1-), U7.9 (NC), U9.2 (CC2)
/USB/USB2_DN: J3.A7 (D-), J3.B7 (D-), U2.T13 (USB_OTG2_DN), U7.5 (D2-), U7.6 (NC)
/USB/USB2_DP: J3.A6 (D+), J3.B6 (D+), U2.U13 (USB_OTG2_DP), U7.4 (D2+), U7.7 (NC)
/USB/USB2_VBUS: C51.1, C110.1, D4.2 (A), J3.A4 (VBUS), J3.A9 (VBUS), J3.B4 (VBUS), J3.B9 (VBUS), R32.1, U8.C2 (VBUS1), U8.D1 (VBUS2), U8.D2 (VBUS3), U9.4 (VBUS_DET), U16.1
/USB/USB_SW_EN: R21.1, U8.A1 (EN), U17.4 (Y)
/USB/USB_VBUS: C6.1, D3.1 (K), D4.1 (K), U5.A2 (IN), U5.B2 (IN)
/USB/VDD_USB_CAP: C52.1, C53.1, U2.R12 (VDD_USB_CAP)
DCDC_3V3: C19.1, C108.1, C109.1, R23.1, R24.1, R25.1, R28.1, R57.1, R58.1, U9.12 (VDD), U14.12 (VDD), U17.5 (VCC), U18.1 (VCC); also elsewhere on the board
GND: C6.2, C7.2, C19.2, C49.2, C50.2, C51.2, C52.2, C53.2, C54.2, C108.2, C109.2, C110.2, C111.2, J2.A1 (GND), J2.A12 (GND), J2.B1 (GND), J2.B12 (GND), J2.S, J3.A1 (GND), J3.A12 (GND), J3.B1 (GND), J3.B12 (GND), J3.S (SHIELD), R21.2, R32.2, R33.2, R59.2, U5.C1 (GND), U5.C2 (OVLO), U6.3 (GND), U6.8 (GND), U7.3 (GND), U7.8 (GND), U8.B3 (GND1), U8.C3 (GND2), U8.D3 (GND3), U9.10 (GND), U9.11 (EN_N), U14.3 (PORT), U14.10 (GND), U14.11 (EN_N), U15.2, U16.2, U17.3 (GND), U18.10 (GND), U18.21 (GND), U19.GND; also elsewhere on the board
I2C1_SCL: U9.8 (SCL/OUT2), U14.8 (SCL/OUT2); also elsewhere on the board
I2C1_SDA: U9.7 (SDA/OUT1), U14.7 (SDA/OUT1); also elsewhere on the board
unnamed: R59.1, U8.A3 (ILIM)
unnamed: R25.2, U8.A2 (~FAULT)
unnamed: R23.2, U9.5 (ADDR/ORIENT)
unnamed: R28.2, U14.5 (ADDR)
unnamed: R34.2, U14.4 (VBUS_DET)
UART2_CTS: U18.17 (B3); also elsewhere on the board
UART2_RTS: U18.16 (B4); also elsewhere on the board
UART2_RX: U18.18 (B2); also elsewhere on the board
UART2_TX: U18.19 (B1); also elsewhere on the board
UART4_RX: U18.13 (B7); also elsewhere on the board
UART4_TX: U18.14 (B6); also elsewhere on the board
UART5_RX: U18.12 (B8); also elsewhere on the board
UART5_TX: U18.15 (B5); also elsewhere on the board
USB1_INT_B: R57.2, U14.6 (INT_N/OUT3); also elsewhere on the board
USB2_ID: R24.2, U9.9 (ID), U17.2 (A); also elsewhere on the board
USB2_INT_B: R58.2, U9.6 (INT_N/OUT3); also elsewhere on the board
VSYS_5V: C7.1, C49.1, C50.1, C54.1, U2.T12 (USB_OTG1_VBUS), U2.U12 (USB_OTG2_VBUS), U5.A1 (OUT), U5.B1 (OUT), U8.B1 (VINT1), U8.B2 (VINT3), U8.C1 (VINT2); also elsewhere on the board

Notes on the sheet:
ADDR tied to VDD: 0x62 I2C address selected. PORT floating: DRP mode selected.
Type-C plug ESD protection
USB2_ID = 0 -> SOURCE USB2_ID = 1 -> SINK
R32 and R33 required to keep USB2_VBUS and USB1_VBUS low from 2.2V to 0.4V
5V, 500mA -> R=35mOhm V_drop(3A) = 100mV
Over voltage protection
Type-C debug mode switch
i.MX6UL USB interface
OVP Voltage = 6.8V
FUSB303 and TUSB320 devices are used to support the USB Type-C Current feature, defined in section 4.6.2.1 [1]. This is not related to the USB Power Delivery feature, here not implemented. The Source can advertise to the Sink the amount of current it can supply: - Default (500 mA for USB 2.0 or 900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
ADDR pulled-up: 0xC2 I2C address selected. PORT tied to GND: UFP mode selected.
Type-C receptacle port controller
R_ILIM = 33 kOhm to GND -> 1.5A
USB 2.0 Type-C plug
Type-C receptacle ESD protection
Type-C plug port controller
USB 2.0 Type-C receptacle
Type-C receptacle power switch
